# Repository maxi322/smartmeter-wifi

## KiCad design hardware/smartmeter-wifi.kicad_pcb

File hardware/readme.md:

# Hardware

**[Render Schematic](https://kicanvas.org/?github=https%3A%2F%2Fgithub.com%2Fmaxi322%2Fsmartmeter-wifi%2Fblob%2Ffeature%2Fhwviewer%2Fhardware%2Fsmartmeter-wifi.kicad_sch)**

**[Render Board](https://kicanvas.org/?github=https%3A%2F%2Fgithub.com%2Fmaxi322%2Fsmartmeter-wifi%2Fblob%2Ffeature%2Fhwviewer%2Fhardware%2Fsmartmeter-wifi.kicad_pcb)**

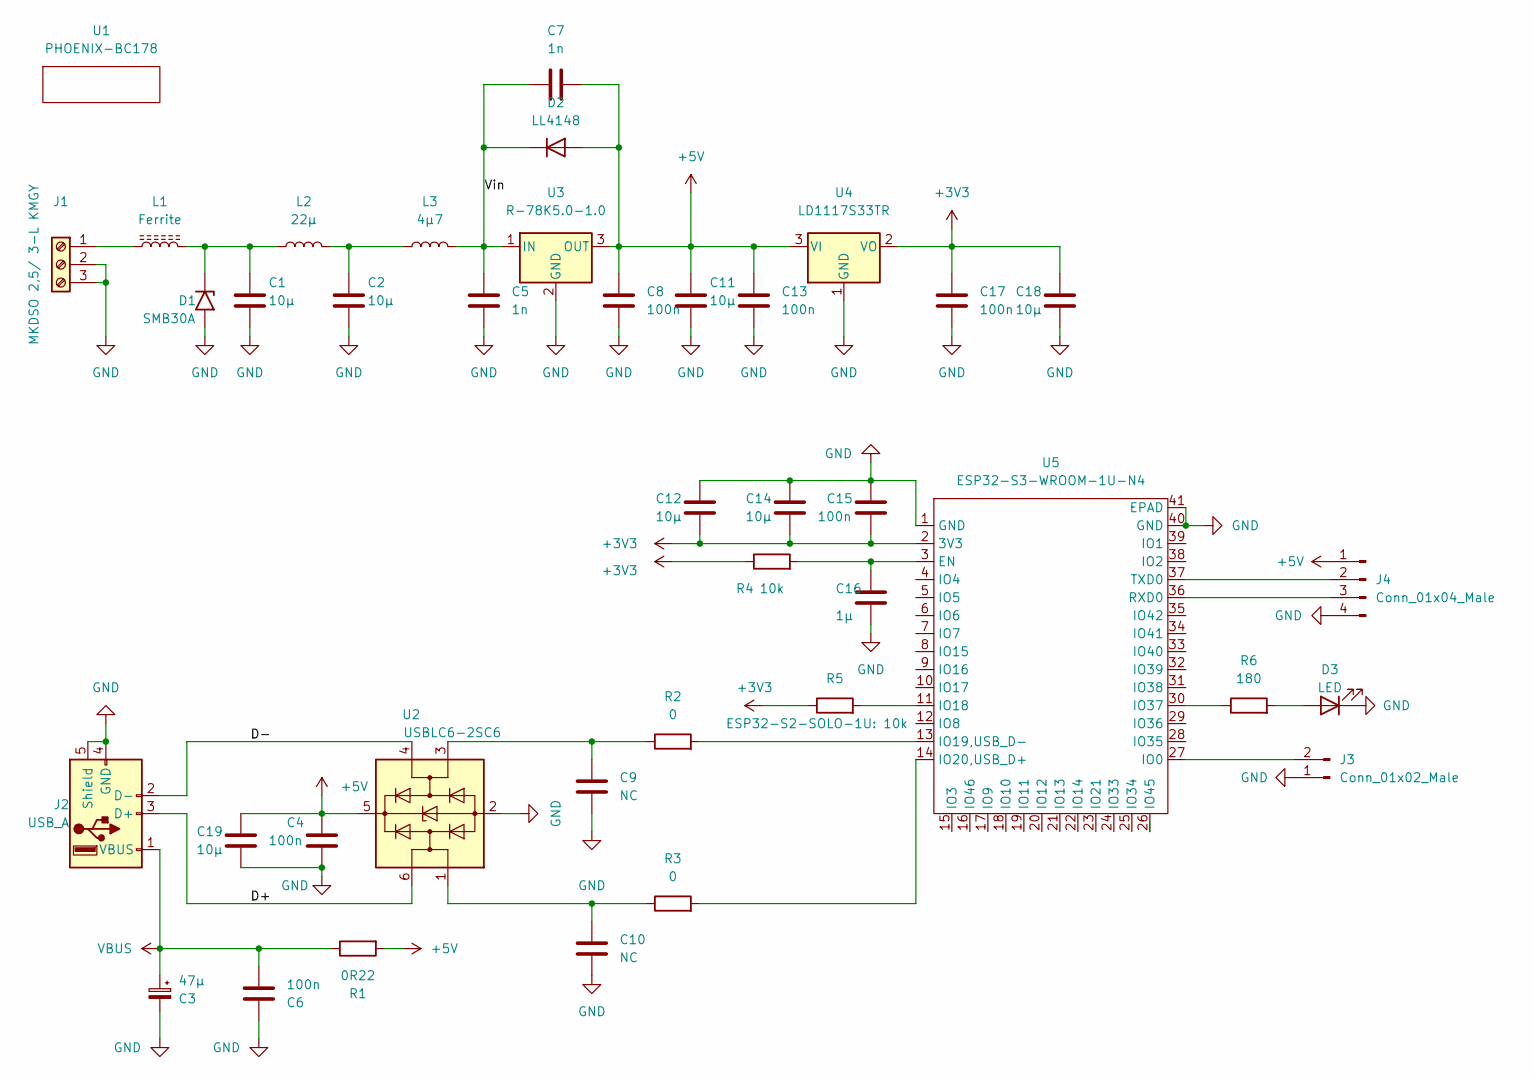
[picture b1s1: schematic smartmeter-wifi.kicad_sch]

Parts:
C1, C2, C11, C12, C14, C18, C19: 10µ; C_1206_3216Metric
C3: 47µ; CP_EIA-3528-15_AVX-H
C4, C6, C8, C13, C15, C17: 100n; C_0603_1608Metric
C5, C7: 1n; C_0603_1608Metric
C9, C10: NC; C_0603_1608Metric
C16: 1µ; C_1206_3216Metric
D1: SMB30A; D_SMB
D2: LL4148; D_MiniMELF
D3: LED; LED_D1.8mm_W1.8mm_H2.4mm_Horizontal_O3.81mm_Z1.6mm
J1: MKDSO 2,5/ 3-L KMGY; phoenix-mkdso-2-5-3-l-kmgy
J2: USB_A; USB_A_Molex_67643_Horizontal
J3: Conn_01x02_Male; PinHeader_1x02_P2.00mm_Horizontal
J4: Conn_01x04_Male; PinHeader_1x04_P2.00mm_Horizontal
L1: Ferrite; L_1806_4516Metric
L2: 22µ; L_1210_3225Metric
L3: 4µ7; L_1210_3225Metric
R1: 0R22; R_0603_1608Metric
R2, R3: 0; R_0603_1608Metric
R4: 10k; R_0603_1608Metric
R5: ESP32-S2-SOLO-1U: 10k; R_0603_1608Metric
R6: 180; R_0603_1608Metric
U1: PHOENIX-BC178; phoenix-bc178-reduced-1
U2: USBLC6-2SC6; SOT-23-6
U3: R-78K5.0-1.0; Converter_DCDC_RECOM_R-78E-0.5_THT
U4: LD1117S33TR; SOT-223-3_TabPin2
U5: ESP32-S3-WROOM-1U-N4; ESP32-S2-SOLO-U

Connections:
+3V3: C12.2, C14.2, C15.2, C17.1, C18.1, R4.1, R5.1, U4.2 (VO), U5.2 (3V3)
+5V: C4.1, C7.2, C8.1, C11.1, C13.1, C19.1, D2.2 (A), J4.1, R1.2, U2.5 (VBUS), U3.3 (OUT), U4.3 (VI)
/D+: J2.3 (D+), U2.6 (I/O1)
/D-: J2.2 (D-), U2.4 (I/O2)
/Vin: C5.1, C7.1, D2.1 (K), L3.2, U3.1 (IN)
GND: C1.2, C2.2, C3.2, C4.2, C5.2, C6.1, C8.2, C9.2, C10.2, C11.2, C12.1, C13.2, C14.1, C15.1, C16.2, C17.2, C18.2, C19.2, D1.2 (A2), D3.1 (K), J1.2, J1.3, J2.4 (GND), J2.5 (Shield), J3.1, J4.4, U2.2 (GND), U3.2 (GND), U4.1 (GND), U5.1 (GND), U5.40 (GND), U5.41 (EPAD)
unnamed: C1.1, D1.1 (A1), L1.2, L2.1
unnamed: C2.1, L2.2, L3.1
unnamed: C9.1, R2.1, U2.3 (I/O2)
unnamed: C10.1, R3.1, U2.1 (I/O1)
unnamed: C16.1, R4.2, U5.3 (EN)
unnamed: D3.2 (A), R6.2
unnamed: J1.1, L1.1
unnamed: J3.2, U5.27 (IO0)
unnamed: J4.2, U5.37 (TXD0)
unnamed: J4.3, U5.36 (RXD0)
unnamed: R2.2, U5.13 (IO19,USB_D-)
unnamed: R3.2, U5.14 (IO20,USB_D+)
unnamed: R5.2, U5.11 (IO18)
unnamed: R6.1, U5.30 (IO37)
VBUS: C3.1, C6.2, J2.1 (VBUS), R1.1

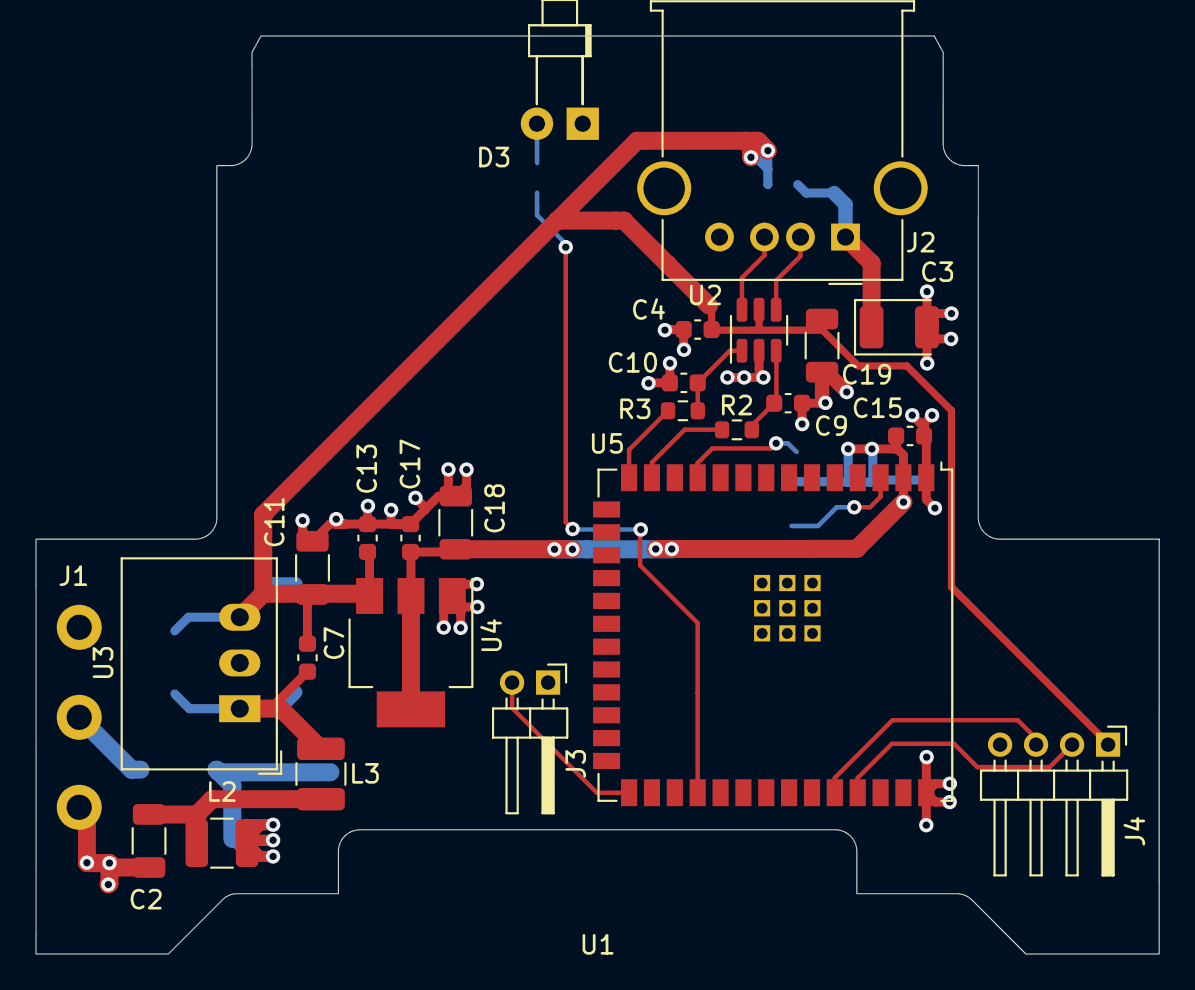
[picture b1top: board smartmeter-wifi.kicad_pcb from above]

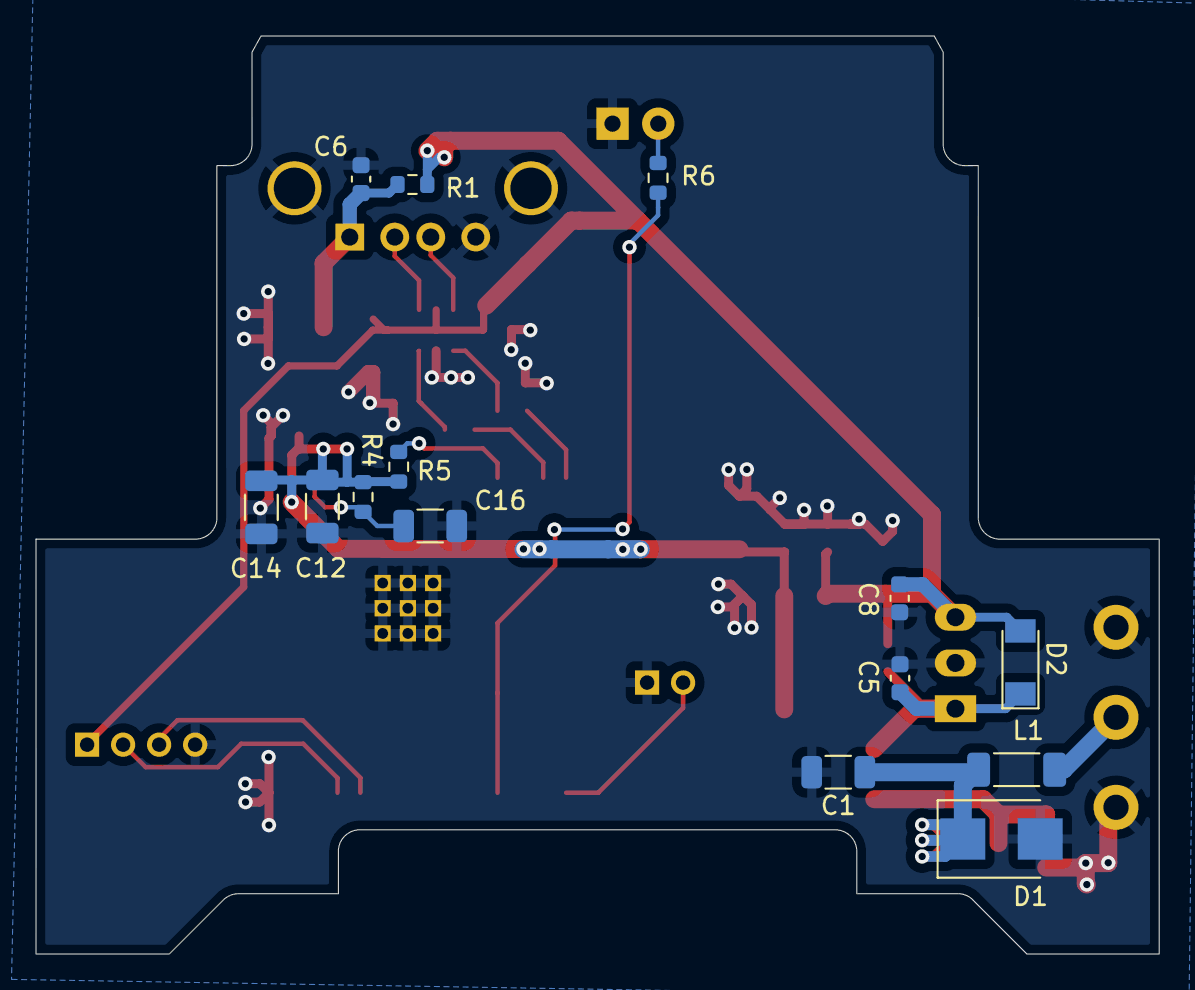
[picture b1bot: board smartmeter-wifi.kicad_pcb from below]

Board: 2 copper layers, 62.4 x 51.0 mm, 40 parts (14 on the bottom side), 21 nets.

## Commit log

2023-08-06 hardware: Add initial design
2023-08-06 firmware: Add initial test version
2023-08-09 hardware: Add images
2023-09-15 firmware: Add initial version
2023-09-16 Firmware: Add coredump section to SPIFFS
2023-11-26 firmware: Reconnect to wlan
2024-03-27 firmware: Update MqttClient and WebServer version
2024-03-27 firmware: Add info page
    Show uptime and wifi info.
2024-05-09 firmware: Connect to MQTT broker if Wifi gets available
    If Wifi was not available during boot up there was not try to connect
    to MQTT broker if Wifi came up.
2024-05-20 firmware: Change USB_DEVICE_PID to 0x6015
    - this change is HW specific
2024-05-20 firmware: Add MQTT user authentication
2024-05-20 firmware: Change wifi password type to 'password'
2024-05-20 test readme
2024-05-25 firmware: Fix MQTT connect
    Do not try to connect if there's no MQTT configuration.
2024-06-01 firmware: split spiffs in two partitions
    this enables making variables persistent over firmware updates of spiffs
2024-06-01 update dependencies
2024-09-01 add custom esp32-s3 4MB board
2024-09-01 update platformio.ini to work with esp32s3 4MB
2024-09-03 fix ESP32-S3 4MB flash
2024-09-03 add .gitignore
2024-09-09 add tool-mkspiffs
2024-09-09 [CI] initial
